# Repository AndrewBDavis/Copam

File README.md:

Copam K-430 Hotswap USB PCB Retrofit
=====================

Refer to PDF for full detailed buildlog

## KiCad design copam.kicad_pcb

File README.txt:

Copam K-430 Alps Electric USB Hotswap Retrofit PCB Project

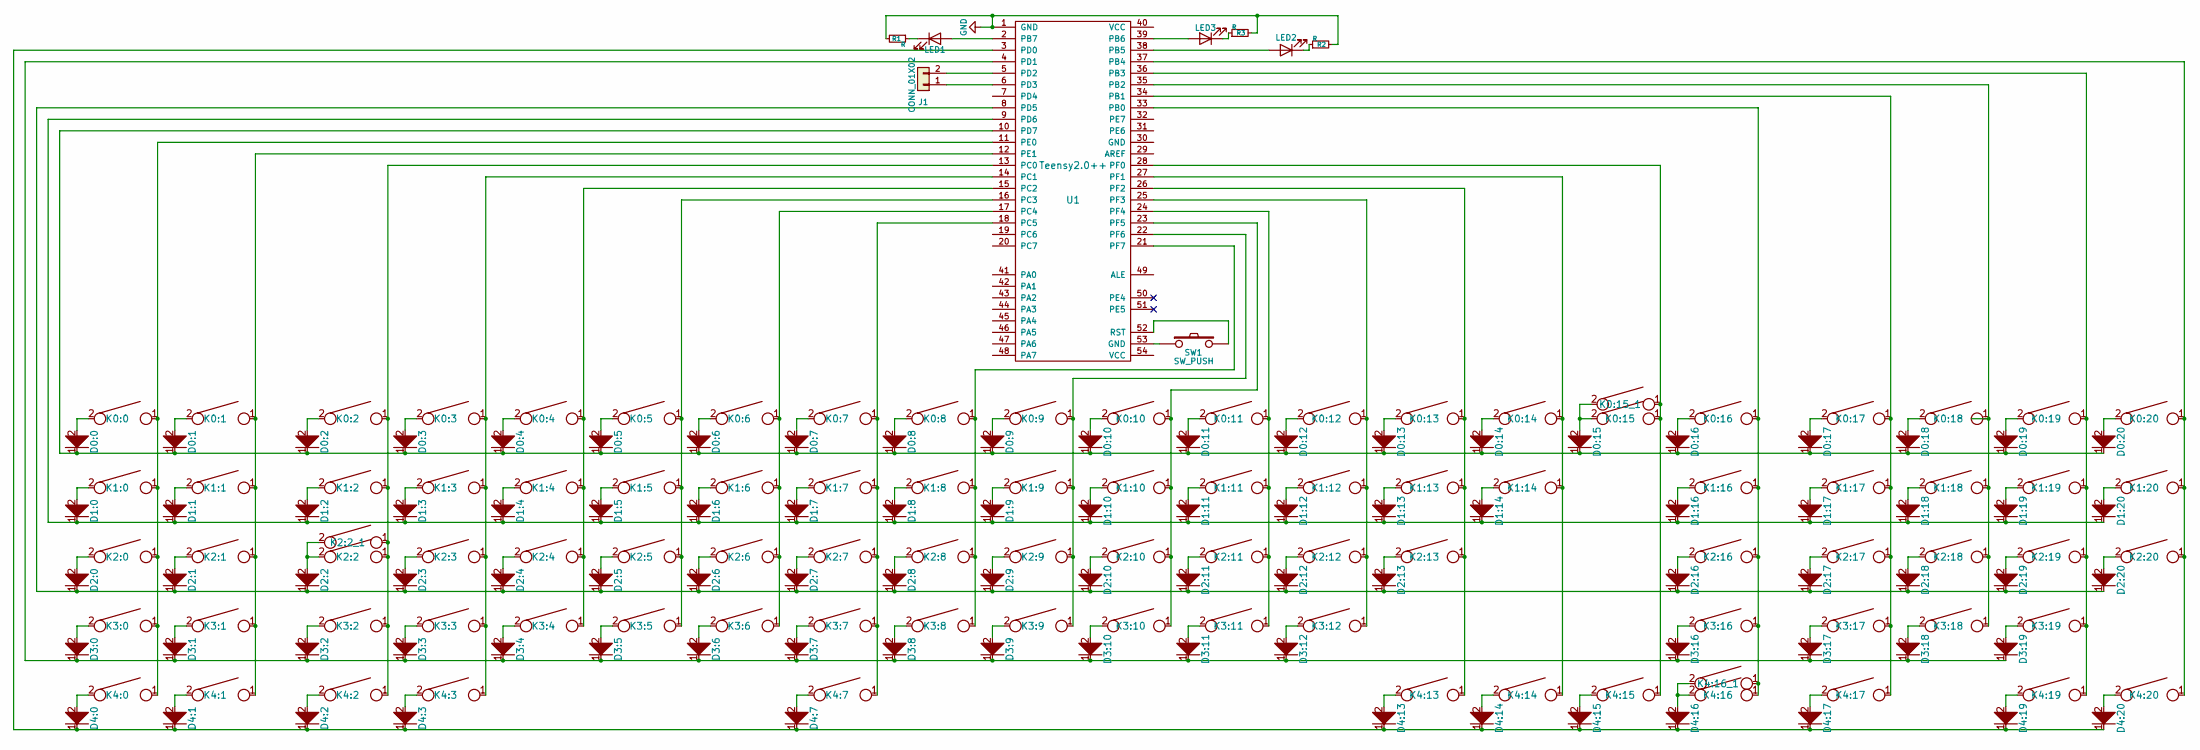
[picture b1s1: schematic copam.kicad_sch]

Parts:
D0:0, D0:1, D0:2, D0:3, D0:4, D0:5, D0:6, D0:7, D0:8, D0:9, D0:10, D0:11, D0:12, D0:13, D0:14, D0:15, D0:16, D0:17, D0:18, D0:19, D0:20, D1:0, D1:1, D1:2, D1:3, D1:4, D1:5, D1:6, D1:7, D1:8, D1:9, D1:10, D1:11, D1:12, D1:13, D1:14, D1:16, D1:17, D1:18, D1:19, D1:20, D2:0, D2:1, D2:2, D2:3, D2:4, D2:5, D2:6, D2:7, D2:8, D2:9, D2:10, D2:11, D2:12, D2:13, D2:16, D2:17, D2:18, D2:19, D2:20, D3:0, D3:1, D3:2, D3:3, D3:4, D3:5, D3:6, D3:7, D3:8, D3:9, D3:10, D3:11, D3:12, D3:16, D3:17, D3:18, D3:19, D4:0, D4:1, D4:2, D4:3, D4:7, D4:13, D4:14, D4:15, D4:16, D4:17, D4:19, D4:20: D; D_SOD-123
J1: CONN_01X02; PinHeader_1x02_P2.00mm_Vertical
K0:0, K0:1, K0:2, K0:3, K0:4, K0:5, K0:6, K0:7, K0:8, K0:9, K0:10, K0:11, K0:12, K0:13, K0:14, K0:15, K0:16, K0:17, K0:18, K0:19, K0:20, K1:0, K1:1, K1:2, K1:3, K1:4, K1:5, K1:6, K1:7, K1:8, K1:9, K1:10, K1:11, K1:12, K1:13, K1:14, K1:16, K1:17, K1:18, K1:19, K1:20, K2:0, K2:1, K2:2, K2:3, K2:4, K2:5, K2:6, K2:7, K2:8, K2:9, K2:10, K2:11, K2:12, K2:13, K2:16, K2:17, K2:18, K2:19, K2:20, K3:0, K3:1, K3:2, K3:3, K3:4, K3:5, K3:6, K3:7, K3:8, K3:9, K3:10, K3:11, K3:12, K3:16, K3:17, K3:18, K3:19, K4:0, K4:1, K4:2, K4:3, K4:7, K4:13, K4:14, K4:15, K4:16, K4:17, K4:19, K4:20: KEYSW; Alps_Hotswap
K0:15_1, K2:2_1, K4:16_1: KEYSW; Alps_Hotswap_Secondary
LED1, LED2, LED3: 5mm_Rectangular; LED_Rectangular_W5.0mm_H2.0mm
R1, R2, R3: R; R_0805_2012Metric
SW1: SW_PUSH; TE_1825966-1
U1: Teensy2.0++

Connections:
GND: R1.2, R2.2, R3.2, U1.1 (GND)
unnamed: D0:0.1, D0:1.1, D0:2.1, D0:3.1, D0:4.1, D0:5.1, D0:6.1, D0:7.1, D0:8.1, D0:9.1, D0:10.1, D0:11.1, D0:12.1, D0:13.1, D0:14.1, D0:15.1, D0:16.1, D0:17.1, D0:18.1, D0:19.1, D0:20.1, U1.10 (PD7)
unnamed: D0:0.2, K0:0.2
unnamed: D0:1.2, K0:1.2
unnamed: D0:2.2, K0:2.2
unnamed: D0:3.2, K0:3.2
unnamed: D0:4.2, K0:4.2
unnamed: D0:5.2, K0:5.2
unnamed: D0:6.2, K0:6.2
unnamed: D0:7.2, K0:7.2
unnamed: D0:8.2, K0:8.2
unnamed: D0:9.2, K0:9.2
unnamed: D0:10.2, K0:10.2
unnamed: D0:11.2, K0:11.2
unnamed: D0:12.2, K0:12.2
unnamed: D0:13.2, K0:13.2
unnamed: D0:14.2, K0:14.2
unnamed: D0:15.2, K0:15.2, K0:15_1.2
unnamed: D0:16.2, K0:16.2
unnamed: D0:17.2, K0:17.2
unnamed: D0:18.2, K0:18.2
unnamed: D0:19.2, K0:19.2
unnamed: D0:20.2, K0:20.2
unnamed: D1:0.1, D1:1.1, D1:2.1, D1:3.1, D1:4.1, D1:5.1, D1:6.1, D1:7.1, D1:8.1, D1:9.1, D1:10.1, D1:11.1, D1:12.1, D1:13.1, D1:14.1, D1:16.1, D1:17.1, D1:18.1, D1:19.1, D1:20.1, U1.9 (PD6)
unnamed: D1:0.2, K1:0.2
unnamed: D1:1.2, K1:1.2
unnamed: D1:2.2, K1:2.2
unnamed: D1:3.2, K1:3.2
unnamed: D1:4.2, K1:4.2
unnamed: D1:5.2, K1:5.2
unnamed: D1:6.2, K1:6.2
unnamed: D1:7.2, K1:7.2
unnamed: D1:8.2, K1:8.2
unnamed: D1:9.2, K1:9.2
unnamed: D1:10.2, K1:10.2
unnamed: D1:11.2, K1:11.2
unnamed: D1:12.2, K1:12.2
unnamed: D1:13.2, K1:13.2
unnamed: D1:14.2, K1:14.2
unnamed: D1:16.2, K1:16.2
unnamed: D1:17.2, K1:17.2
unnamed: D1:18.2, K1:18.2
unnamed: D1:19.2, K1:19.2
unnamed: D1:20.2, K1:20.2
unnamed: D2:0.1, D2:1.1, D2:2.1, D2:3.1, D2:4.1, D2:5.1, D2:6.1, D2:7.1, D2:8.1, D2:9.1, D2:10.1, D2:11.1, D2:12.1, D2:13.1, D2:16.1, D2:17.1, D2:18.1, D2:19.1, D2:20.1, U1.8 (PD5)
unnamed: D2:0.2, K2:0.2
unnamed: D2:1.2, K2:1.2
unnamed: D2:2.2, K2:2.2, K2:2_1.2
unnamed: D2:3.2, K2:3.2
unnamed: D2:4.2, K2:4.2
unnamed: D2:5.2, K2:5.2
unnamed: D2:6.2, K2:6.2
unnamed: D2:7.2, K2:7.2
unnamed: D2:8.2, K2:8.2
unnamed: D2:9.2, K2:9.2
unnamed: D2:10.2, K2:10.2
unnamed: D2:11.2, K2:11.2
unnamed: D2:12.2, K2:12.2
unnamed: D2:13.2, K2:13.2
unnamed: D2:16.2, K2:16.2
unnamed: D2:17.2, K2:17.2
unnamed: D2:18.2, K2:18.2
unnamed: D2:19.2, K2:19.2
unnamed: D2:20.2, K2:20.2
unnamed: D3:0.1, D3:1.1, D3:2.1, D3:3.1, D3:4.1, D3:5.1, D3:6.1, D3:7.1, D3:8.1, D3:9.1, D3:10.1, D3:11.1, D3:12.1, D3:16.1, D3:17.1, D3:18.1, D3:19.1, U1.4 (PD1)
unnamed: D3:0.2, K3:0.2
unnamed: D3:1.2, K3:1.2
unnamed: D3:2.2, K3:2.2
unnamed: D3:3.2, K3:3.2
unnamed: D3:4.2, K3:4.2
unnamed: D3:5.2, K3:5.2
unnamed: D3:6.2, K3:6.2
unnamed: D3:7.2, K3:7.2
unnamed: D3:8.2, K3:8.2
unnamed: D3:9.2, K3:9.2
unnamed: D3:10.2, K3:10.2
unnamed: D3:11.2, K3:11.2
unnamed: D3:12.2, K3:12.2
unnamed: D3:16.2, K3:16.2
unnamed: D3:17.2, K3:17.2
unnamed: D3:18.2, K3:18.2
unnamed: D3:19.2, K3:19.2
unnamed: D4:0.1, D4:1.1, D4:2.1, D4:3.1, D4:7.1, D4:13.1, D4:14.1, D4:15.1, D4:16.1, D4:17.1, D4:19.1, D4:20.1, U1.3 (PD0)
unnamed: D4:0.2, K4:0.2
unnamed: D4:1.2, K4:1.2
unnamed: D4:2.2, K4:2.2
unnamed: D4:3.2, K4:3.2
unnamed: D4:7.2, K4:7.2
unnamed: D4:13.2, K4:13.2
unnamed: D4:14.2, K4:14.2
unnamed: D4:15.2, K4:15.2
unnamed: D4:16.2, K4:16.2, K4:16_1.2
unnamed: D4:17.2, K4:17.2
unnamed: D4:19.2, K4:19.2
unnamed: D4:20.2, K4:20.2
unnamed: J1.1, U1.6 (PD3)
unnamed: J1.2, U1.5 (PD2)
unnamed: K0:0.1, K1:0.1, K2:0.1, K3:0.1, K4:0.1, U1.11 (PE0)
unnamed: K0:1.1, K1:1.1, K2:1.1, K3:1.1, K4:1.1, U1.12 (PE1)
unnamed: K0:2.1, K1:2.1, K2:2.1, K2:2_1.1, K3:2.1, K4:2.1, U1.13 (PC0)
unnamed: K0:3.1, K1:3.1, K2:3.1, K3:3.1, K4:3.1, U1.14 (PC1)
unnamed: K0:4.1, K1:4.1, K2:4.1, K3:4.1, U1.15 (PC2)
unnamed: K0:5.1, K1:5.1, K2:5.1, K3:5.1, U1.16 (PC3)
unnamed: K0:6.1, K1:6.1, K2:6.1, K3:6.1, U1.17 (PC4)
unnamed: K0:7.1, K1:7.1, K2:7.1, K3:7.1, K4:7.1, U1.18 (PC5)
unnamed: K0:8.1, K1:8.1, K2:8.1, K3:8.1, U1.21 (PF7)
unnamed: K0:9.1, K1:9.1, K2:9.1, K3:9.1, U1.22 (PF6)
unnamed: K0:10.1, K1:10.1, K2:10.1, K3:10.1, U1.23 (PF5)
unnamed: K0:11.1, K1:11.1, K2:11.1, K3:11.1, U1.24 (PF4)
unnamed: K0:12.1, K1:12.1, K2:12.1, K3:12.1, U1.25 (PF3)
unnamed: K0:13.1, K1:13.1, K2:13.1, K4:13.1, U1.26 (PF2)
unnamed: K0:14.1, K1:14.1, K4:14.1, U1.27 (PF1)
unnamed: K0:15.1, K0:15_1.1, K4:15.1, U1.28 (PF0)
unnamed: K0:16.1, K1:16.1, K2:16.1, K3:16.1, K4:16.1, K4:16_1.1, U1.33 (PB0)
unnamed: K0:17.1, K1:17.1, K2:17.1, K3:17.1, K4:17.1, U1.34 (PB1)
unnamed: K0:18.1, K1:18.1, K2:18.1, K3:18.1, U1.35 (PB2)
unnamed: K0:19.1, K1:19.1, K2:19.1, K3:19.1, K4:19.1, U1.36 (PB3)
unnamed: K0:20.1, K1:20.1, K2:20.1, K4:20.1, U1.37 (PB4)
unnamed: LED1.1 (K), R1.1
unnamed: LED1.2 (A), U1.2 (PB7)
unnamed: LED2.1 (K), R2.1
unnamed: LED2.2 (A), U1.38 (PB5)
unnamed: LED3.1 (K), R3.1
unnamed: LED3.2 (A), U1.39 (PB6)
unnamed: SW1.1, U1.53 (GND)
unnamed: SW1.2, U1.52 (RST)

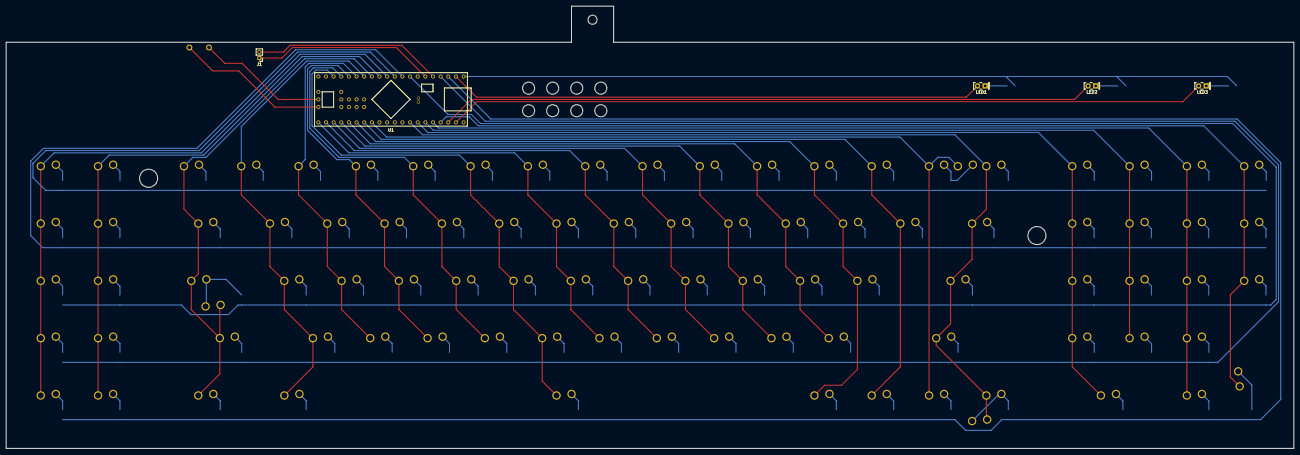
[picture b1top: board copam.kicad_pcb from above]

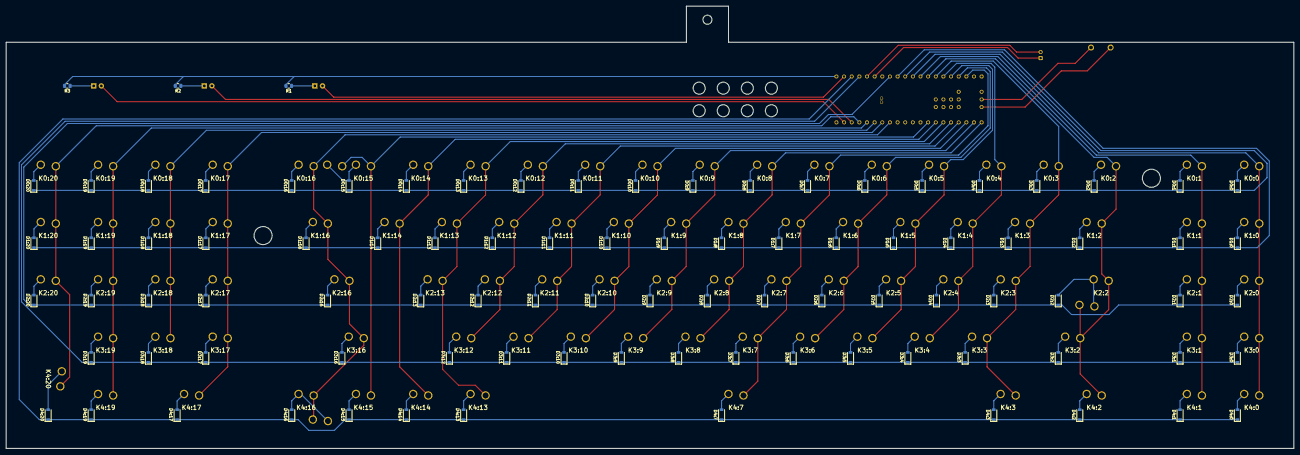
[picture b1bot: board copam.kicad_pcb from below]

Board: 2 copper layers, 428.0 x 147.0 mm, 190 parts (92 on the bottom side), 126 nets.

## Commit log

2022-03-14 Migration to Kicad 6
